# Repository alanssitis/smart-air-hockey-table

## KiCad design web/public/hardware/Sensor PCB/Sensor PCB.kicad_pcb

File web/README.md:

# Better Website

Just a better site in every way.

All settings are set properly for copy-and-paste into the `/web` directory
of the shay drive. All that needs to be done is to build it.

## Installing `npm`

I use `nvm` to manage node versions. My local machine is running `v18.16.0` as
of Sep 5, 2023.

## Building the site

First, install all dependencies with

```
npm install .
```

Than, build the project with

```
npm run build
```

This will create all the requisites in `/dist`. The contents of `/dist` can
be copied to the shay `/web` directory.

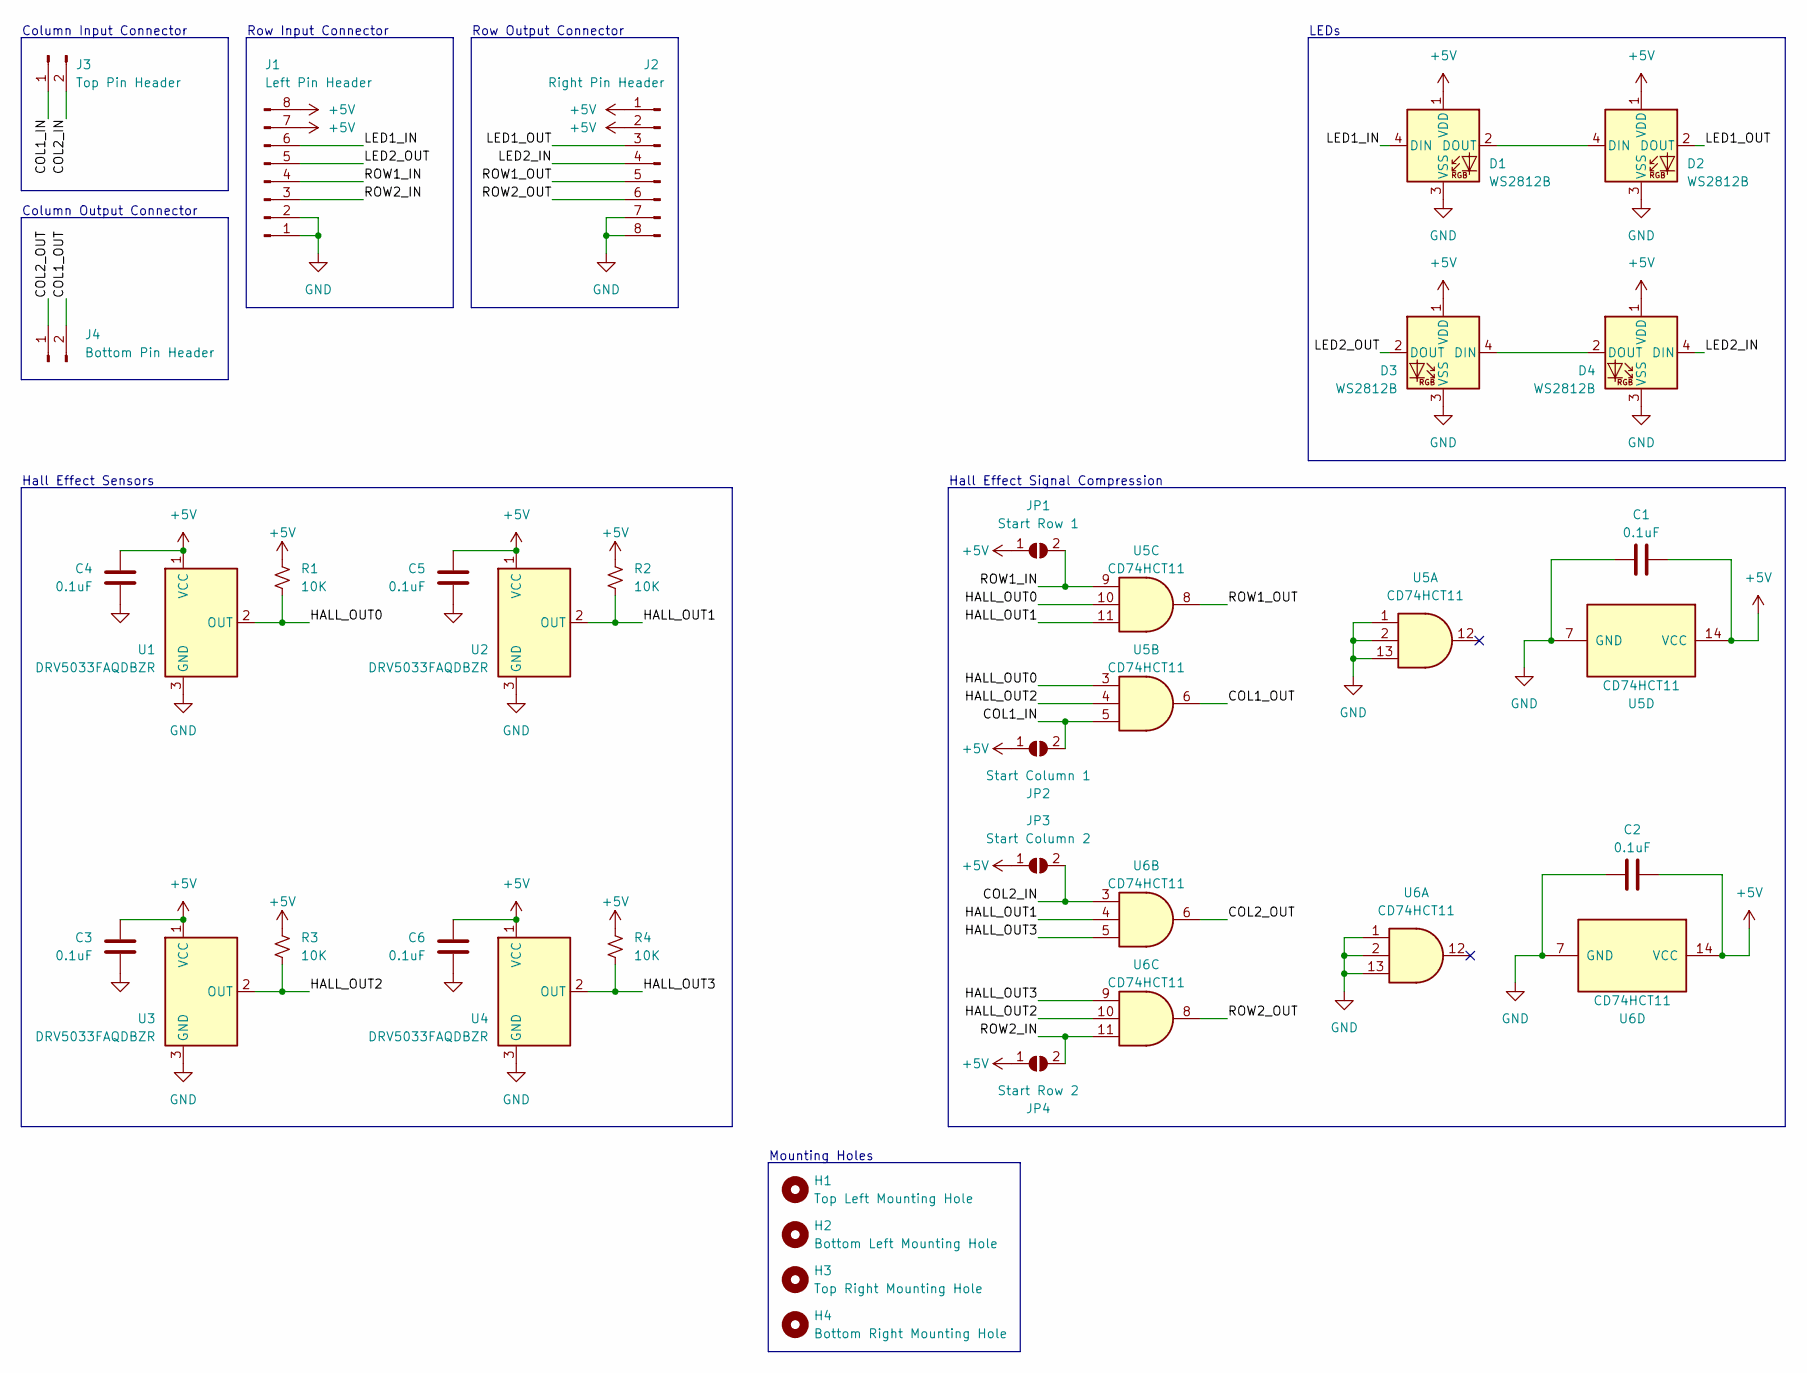
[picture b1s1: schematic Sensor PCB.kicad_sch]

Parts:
C1, C2, C3, C4, C5, C6: 0.1uF; C_0805_2012Metric_Pad1.18x1.45mm_HandSolder; JLCPCB Part # C49678
D1, D2, D3, D4: WS2812B; LED_WS2812B_PLCC4_5.0x5.0mm_P3.2mm; JLCPCB Part # C4154882
H1: Top Left Mounting Hole; MountingHole_2.7mm_M2.5
H2: Bottom Left Mounting Hole; MountingHole_2.7mm_M2.5
H3: Top Right Mounting Hole; MountingHole_2.7mm_M2.5
H4: Bottom Right Mounting Hole; MountingHole_2.7mm_M2.5
J1: Left Pin Header; PinHeader_1x08_P2.54mm_Horizontal; JLCPCB Part # C492416
J2: Right Pin Header; PinHeader_1x08_P2.54mm_Horizontal; JLCPCB Part # C492416
J3: Top Pin Header; PinHeader_1x02_P2.54mm_Horizontal; JLCPCB Part # C492410
J4: Bottom Pin Header; PinHeader_1x02_P2.54mm_Horizontal; JLCPCB Part # C492410
JP1: Start Row 1; SolderJumper-2_P1.3mm_Open_TrianglePad1.0x1.5mm
JP2: Start Column 1; SolderJumper-2_P1.3mm_Open_TrianglePad1.0x1.5mm
JP3: Start Column 2; SolderJumper-2_P1.3mm_Open_TrianglePad1.0x1.5mm
JP4: Start Row 2; SolderJumper-2_P1.3mm_Open_TrianglePad1.0x1.5mm
R1, R2, R3, R4: 10K; R_0805_2012Metric_Pad1.20x1.40mm_HandSolder; JLCPCB Part # C100047
U1, U2, U3, U4: DRV5033FAQDBZR; SOT-23; JLCPCB Part # C2655029
U5, U6: CD74HCT11; SOIC-14_3.9x8.7mm_P1.27mm; JLCPCB Part # C7643

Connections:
+5V: C1.1, C2.1, C3.1, C4.1, C5.1, C6.1, D1.1 (VDD), D2.1 (VDD), D3.1 (VDD), D4.1 (VDD), J1.7, J1.8, J2.1, J2.2, JP1.1 (A), JP2.1 (A), JP3.1 (A), JP4.1 (A), R1.1, R2.1, R3.1, R4.1, U1.1 (VCC), U2.1 (VCC), U3.1 (VCC), U4.1 (VCC), U5.14 (VCC), U6.14 (VCC)
/COL1_IN: J3.1, JP2.2 (B), U5.5
/COL1_OUT: J4.2, U5.6
/COL2_IN: J3.2, JP3.2 (B), U6.3
/COL2_OUT: J4.1, U6.6
/HALL_OUT0: R1.2, U1.2 (OUT), U5.3, U5.10
/HALL_OUT1: R2.2, U2.2 (OUT), U5.11, U6.4
/HALL_OUT2: R3.2, U3.2 (OUT), U5.4, U6.10
/HALL_OUT3: R4.2, U4.2 (OUT), U6.5, U6.9
/LED1_IN: D1.4 (DIN), J1.6
/LED1_OUT: D2.2 (DOUT), J2.3
/LED2_IN: D4.4 (DIN), J2.4
/LED2_OUT: D3.2 (DOUT), J1.5
/ROW1_IN: J1.4, JP1.2 (B), U5.9
/ROW1_OUT: J2.5, U5.8
/ROW2_IN: J1.3, JP4.2 (B), U6.11
/ROW2_OUT: J2.6, U6.8
GND: C1.2, C2.2, C3.2, C4.2, C5.2, C6.2, D1.3 (VSS), D2.3 (VSS), D3.3 (VSS), D4.3 (VSS), J1.1, J1.2, J2.7, J2.8, U1.3 (GND), U2.3 (GND), U3.3 (GND), U4.3 (GND), U5.1, U5.2, U5.7 (GND), U5.13, U6.1, U6.2, U6.7 (GND), U6.13
unnamed: D1.2 (DOUT), D2.4 (DIN)
unnamed: D3.4 (DIN), D4.2 (DOUT)

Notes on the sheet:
Hall Effect Sensors
Column Input Connector
Row Output Connector
Column Output Connector
Hall Effect Signal Compression
Mounting Holes
LEDs
Row Input Connector

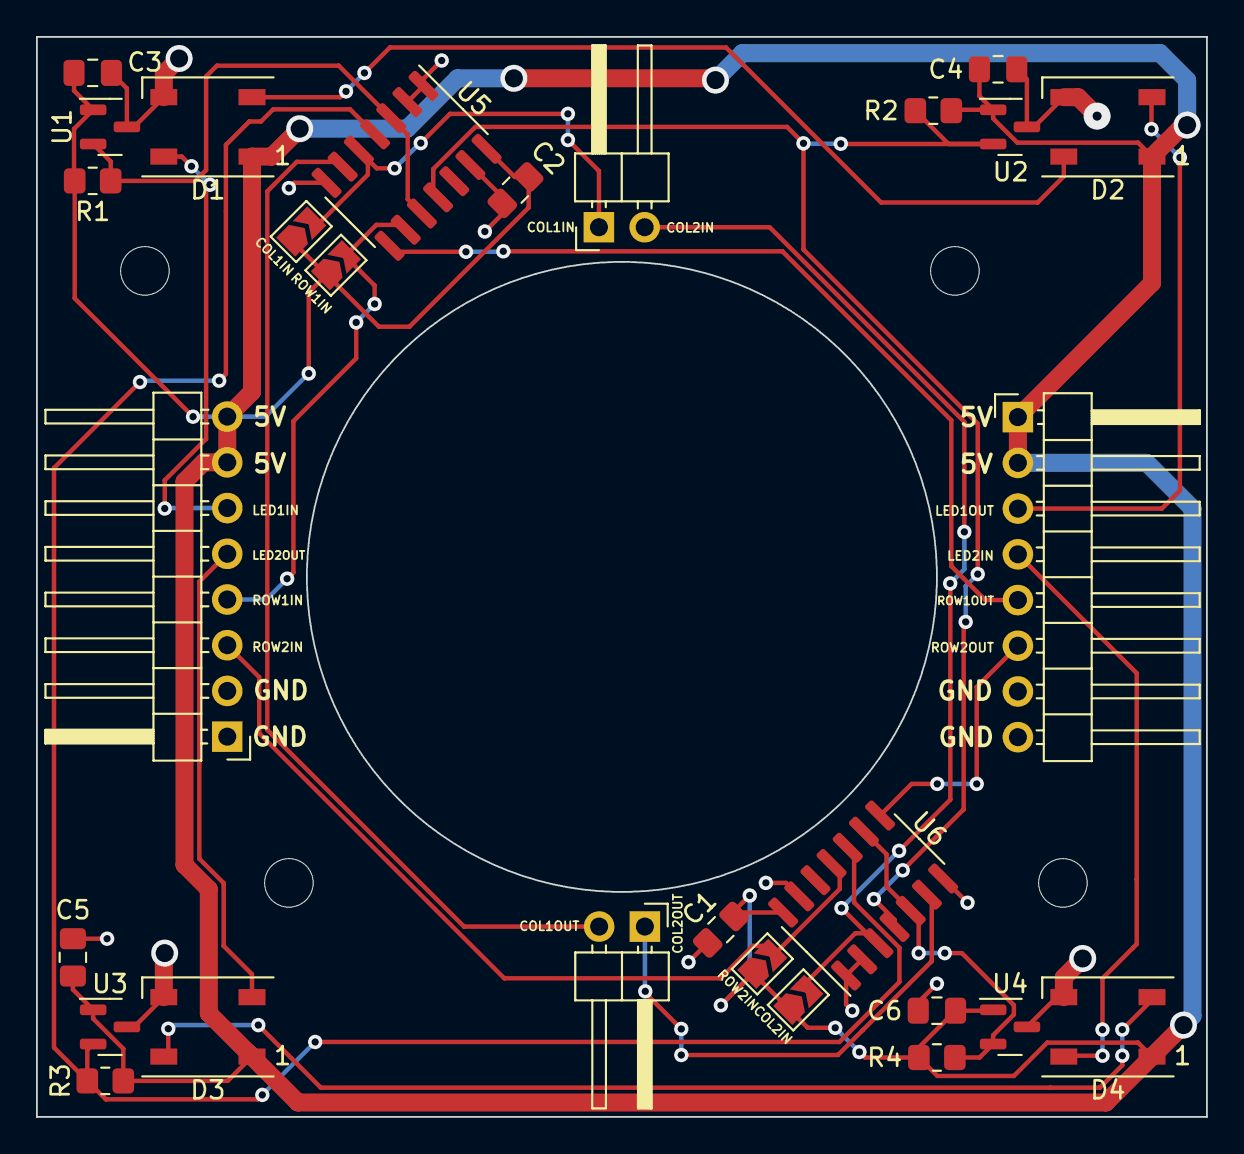
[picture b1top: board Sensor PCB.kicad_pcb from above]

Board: 2 copper layers, 65.0 x 60.0 mm, 32 parts (0 on the bottom side), 20 nets.

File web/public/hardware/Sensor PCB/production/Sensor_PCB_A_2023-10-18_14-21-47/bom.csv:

Designator,Footprint,Quantity,Value,LCSC Part #
"C1, C2, C3, C4, C5, C6",0805,6,0.1uF,C49678
D1,LED_WS2812B_PLCC4_5.0x5.0mm_P3.2mm,1,WS2812B,
"D2, D3, D4",LED_WS2812B_PLCC4_5.0x5.0mm_P3.2mm,3,WS2812B,C4154882
H1,MountingHole_2.7mm_M2.5,1,Top Left Mounting Hole,
H2,MountingHole_2.7mm_M2.5,1,Bottom Left Mounting Hole,
H3,MountingHole_2.7mm_M2.5,1,Top Right Mounting Hole,
H4,MountingHole_2.7mm_M2.5,1,Bottom Right Mounting Hole,
J1,PinHeader_1x08_P2.54mm_Horizontal,1,Left Pin Header,C492416
J2,PinHeader_1x08_P2.54mm_Horizontal,1,Right Pin Header,C492416
J3,PinHeader_1x02_P2.54mm_Horizontal,1,Top Pin Header,C492410
J4,PinHeader_1x02_P2.54mm_Horizontal,1,Bottom Pin Header,C492410
JP1,SolderJumper-2_P1.3mm_Open_TrianglePad1.0x1.5mm,1,Start Row 1,
JP2,SolderJumper-2_P1.3mm_Open_TrianglePad1.0x1.5mm,1,Start Column 1,
JP3,SolderJumper-2_P1.3mm_Open_TrianglePad1.0x1.5mm,1,Start Column 2,
JP4,SolderJumper-2_P1.3mm_Open_TrianglePad1.0x1.5mm,1,Start Row 2,
"R1, R2, R3, R4",0805,4,10K,C100047
"U1, U2, U3, U4",SOT-23,4,DRV5033FAQDBZR,C2655029
"U5, U6",SOIC-14_3.9x8.7mm_P1.27mm,2,CD74HCT11,C7643

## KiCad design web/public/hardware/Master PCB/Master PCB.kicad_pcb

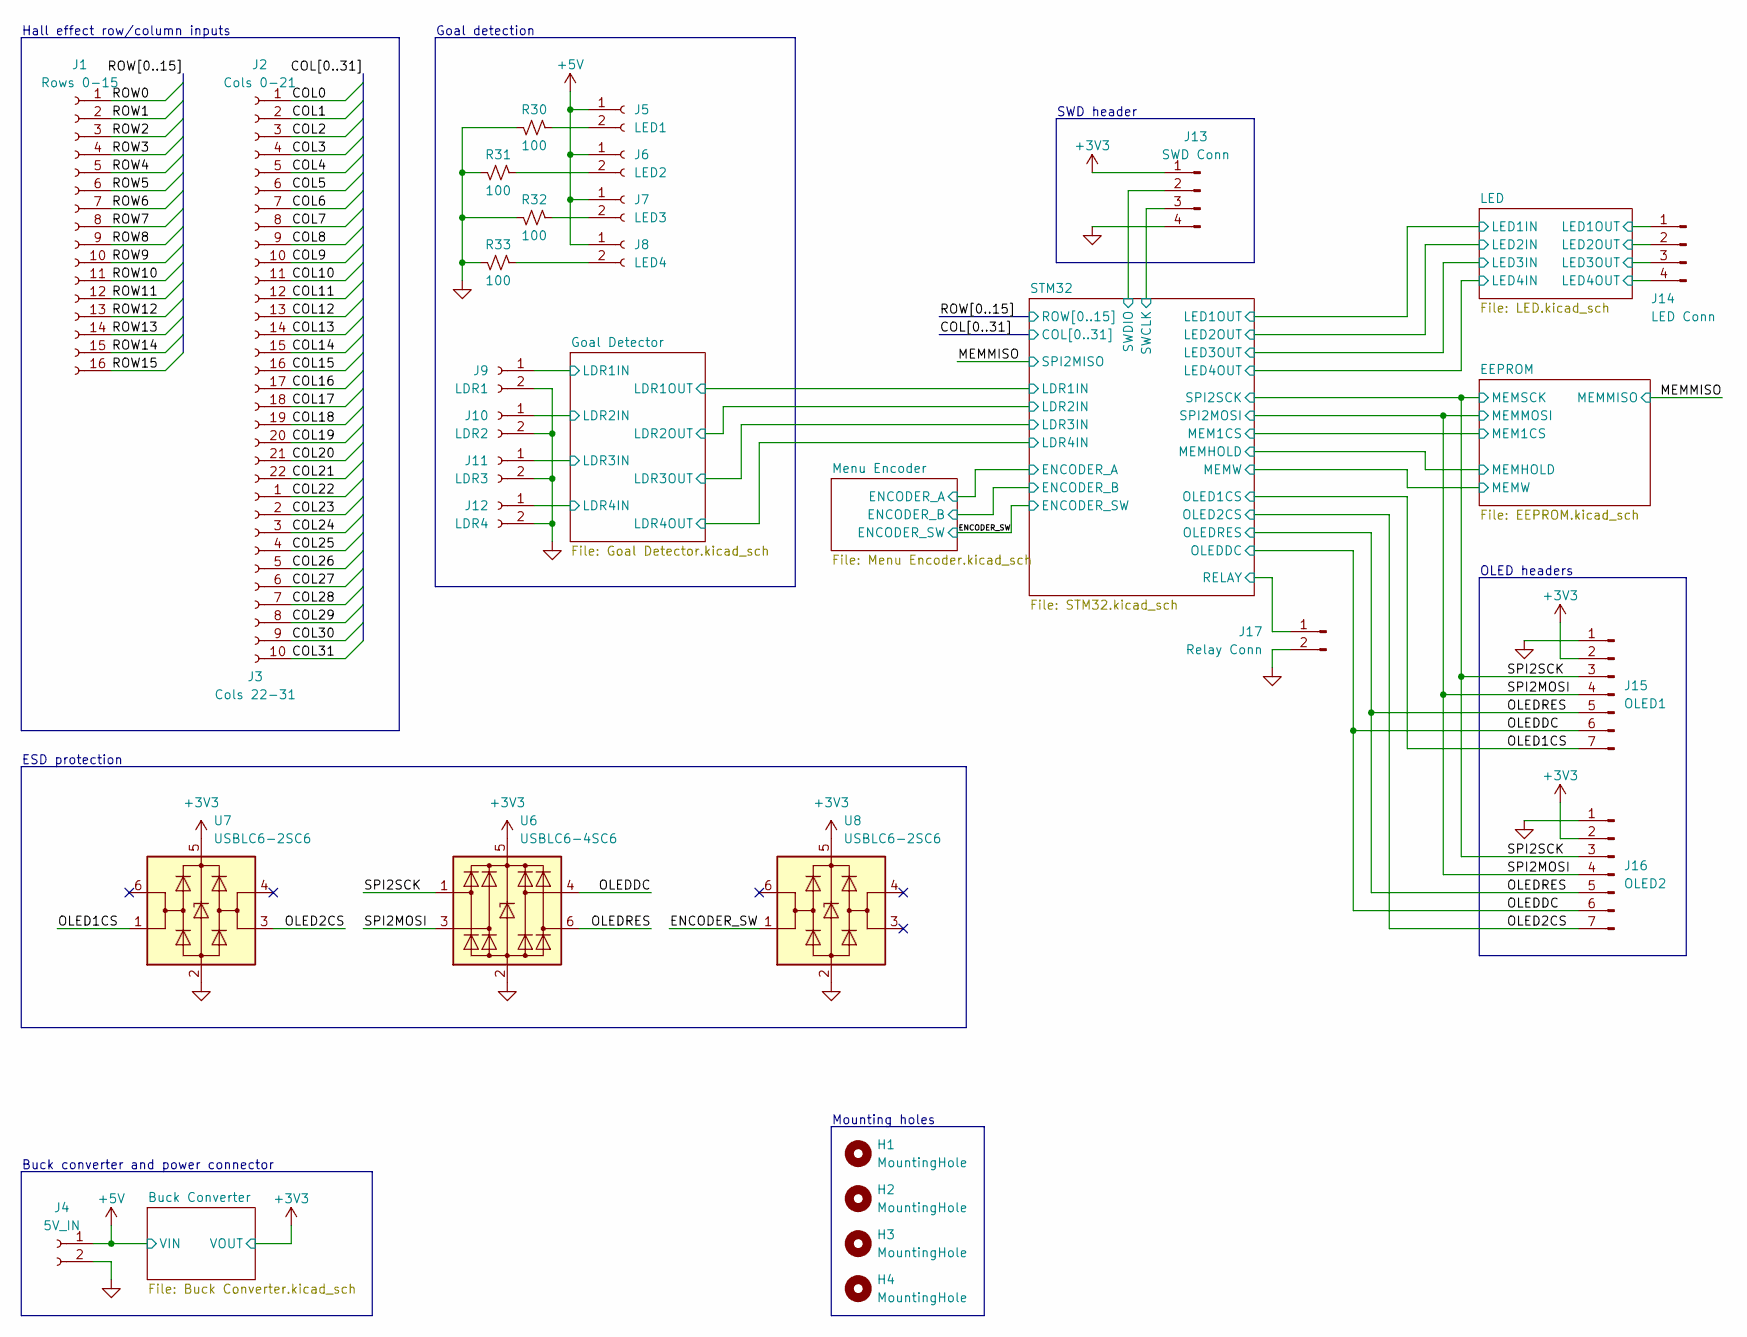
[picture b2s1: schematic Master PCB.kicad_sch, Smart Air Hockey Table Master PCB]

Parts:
H1, H2, H3, H4: MountingHole; MountingHole_3.2mm_M3
J1: Rows 0-15; PinHeader_1x16_P2.54mm_Vertical
J2: Cols 0-21; PinHeader_1x22_P2.54mm_Vertical
J3: Cols 22-31; PinHeader_1x10_P2.54mm_Vertical
J4: 5V_IN; JST_PH_B2B-PH-K_1x02_P2.00mm_Vertical
J5: LED1; JST_PH_B2B-PH-K_1x02_P2.00mm_Vertical
J6: LED2; JST_PH_B2B-PH-K_1x02_P2.00mm_Vertical
J7: LED3; JST_PH_B2B-PH-K_1x02_P2.00mm_Vertical
J8: LED4; JST_PH_B2B-PH-K_1x02_P2.00mm_Vertical
J9: LDR1; JST_PH_B2B-PH-K_1x02_P2.00mm_Vertical
J10: LDR2; JST_PH_B2B-PH-K_1x02_P2.00mm_Vertical
J11: LDR3; JST_PH_B2B-PH-K_1x02_P2.00mm_Vertical
J12: LDR4; JST_PH_B2B-PH-K_1x02_P2.00mm_Vertical
J13: SWD Conn; PinHeader_1x04_P2.54mm_Vertical
J14: LED Conn; PinHeader_1x04_P2.54mm_Vertical
J15: OLED1; JST_PH_B7B-PH-K_1x07_P2.00mm_Vertical
J16: OLED2; JST_PH_B7B-PH-K_1x07_P2.00mm_Vertical
J17: Relay Conn; JST_PH_B2B-PH-K_1x02_P2.00mm_Vertical
R30, R31, R32, R33: 100; R_0805_2012Metric_Pad1.20x1.40mm_HandSolder
U6: USBLC6-4SC6; SOT-23-6
U7, U8: USBLC6-2SC6; SOT-23-6

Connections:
/COL0: J2.1; also elsewhere on the board
/COL1: J2.2; also elsewhere on the board
/COL2: J2.3; also elsewhere on the board
/COL3: J2.4; also elsewhere on the board
/COL4: J2.5; also elsewhere on the board
/COL5: J2.6; also elsewhere on the board
/COL6: J2.7; also elsewhere on the board
/COL7: J2.8; also elsewhere on the board
/COL8: J2.9; also elsewhere on the board
/COL9: J2.10; also elsewhere on the board
/COL10: J2.11; also elsewhere on the board
/COL11: J2.12; also elsewhere on the board
/COL12: J2.13; also elsewhere on the board
/COL13: J2.14; also elsewhere on the board
/COL14: J2.15; also elsewhere on the board
/COL15: J2.16; also elsewhere on the board
/COL16: J2.17; also elsewhere on the board
/COL17: J2.18; also elsewhere on the board
/COL18: J2.19; also elsewhere on the board
/COL19: J2.20; also elsewhere on the board
/COL20: J2.21; also elsewhere on the board
/COL21: J2.22; also elsewhere on the board
/COL22: J3.1; also elsewhere on the board
/COL23: J3.2; also elsewhere on the board
/COL24: J3.3; also elsewhere on the board
/COL25: J3.4; also elsewhere on the board
/COL26: J3.5; also elsewhere on the board
/COL27: J3.6; also elsewhere on the board
/COL28: J3.7; also elsewhere on the board
/COL29: J3.8; also elsewhere on the board
/COL30: J3.9; also elsewhere on the board
/COL31: J3.10; also elsewhere on the board
/ENCODER_SW: U8.1 (I/O1); also elsewhere on the board
/Goal Detector/LDR1IN: J9.1; also elsewhere on the board
/Goal Detector/LDR2IN: J10.1; also elsewhere on the board
/Goal Detector/LDR3IN: J11.1; also elsewhere on the board
/Goal Detector/LDR4IN: J12.1; also elsewhere on the board
/LED/LED1OUT: J14.1; also elsewhere on the board
/LED/LED2OUT: J14.2; also elsewhere on the board
/LED/LED3OUT: J14.3; also elsewhere on the board
/LED/LED4OUT: J14.4; also elsewhere on the board
/OLED1CS: J15.7, U7.1 (I/O1); also elsewhere on the board
/OLED2CS: J16.7, U7.3 (I/O2); also elsewhere on the board
/OLEDDC: J15.6, J16.6, U6.4 (I/O3); also elsewhere on the board
/OLEDRES: J15.5, J16.5, U6.6 (I/O4); also elsewhere on the board
/ROW0: J1.1; also elsewhere on the board
/ROW1: J1.2; also elsewhere on the board
/ROW2: J1.3; also elsewhere on the board
/ROW3: J1.4; also elsewhere on the board
/ROW4: J1.5; also elsewhere on the board
/ROW5: J1.6; also elsewhere on the board
/ROW6: J1.7; also elsewhere on the board
/ROW7: J1.8; also elsewhere on the board
/ROW8: J1.9; also elsewhere on the board
/ROW9: J1.10; also elsewhere on the board
/ROW10: J1.11; also elsewhere on the board
/ROW11: J1.12; also elsewhere on the board
/ROW12: J1.13; also elsewhere on the board
/ROW13: J1.14; also elsewhere on the board
/ROW14: J1.15; also elsewhere on the board
/ROW15: J1.16; also elsewhere on the board
/SPI2SCK: J15.3, J16.3, U6.1 (I/O1); also elsewhere on the board
/STM32/RELAY: J17.1; also elsewhere on the board
/STM32/SWCLK: J13.3; also elsewhere on the board
/STM32/SWDIO: J13.2; also elsewhere on the board
unnamed: J5.2, R30.1
unnamed: J6.2, R31.1
unnamed: J7.2, R32.1
unnamed: J8.2, R33.1

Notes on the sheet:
Mounting holes
Hall effect row/column inputs
SWD header
ESD protection
OLED headers
Buck converter and power connector
Goal detection

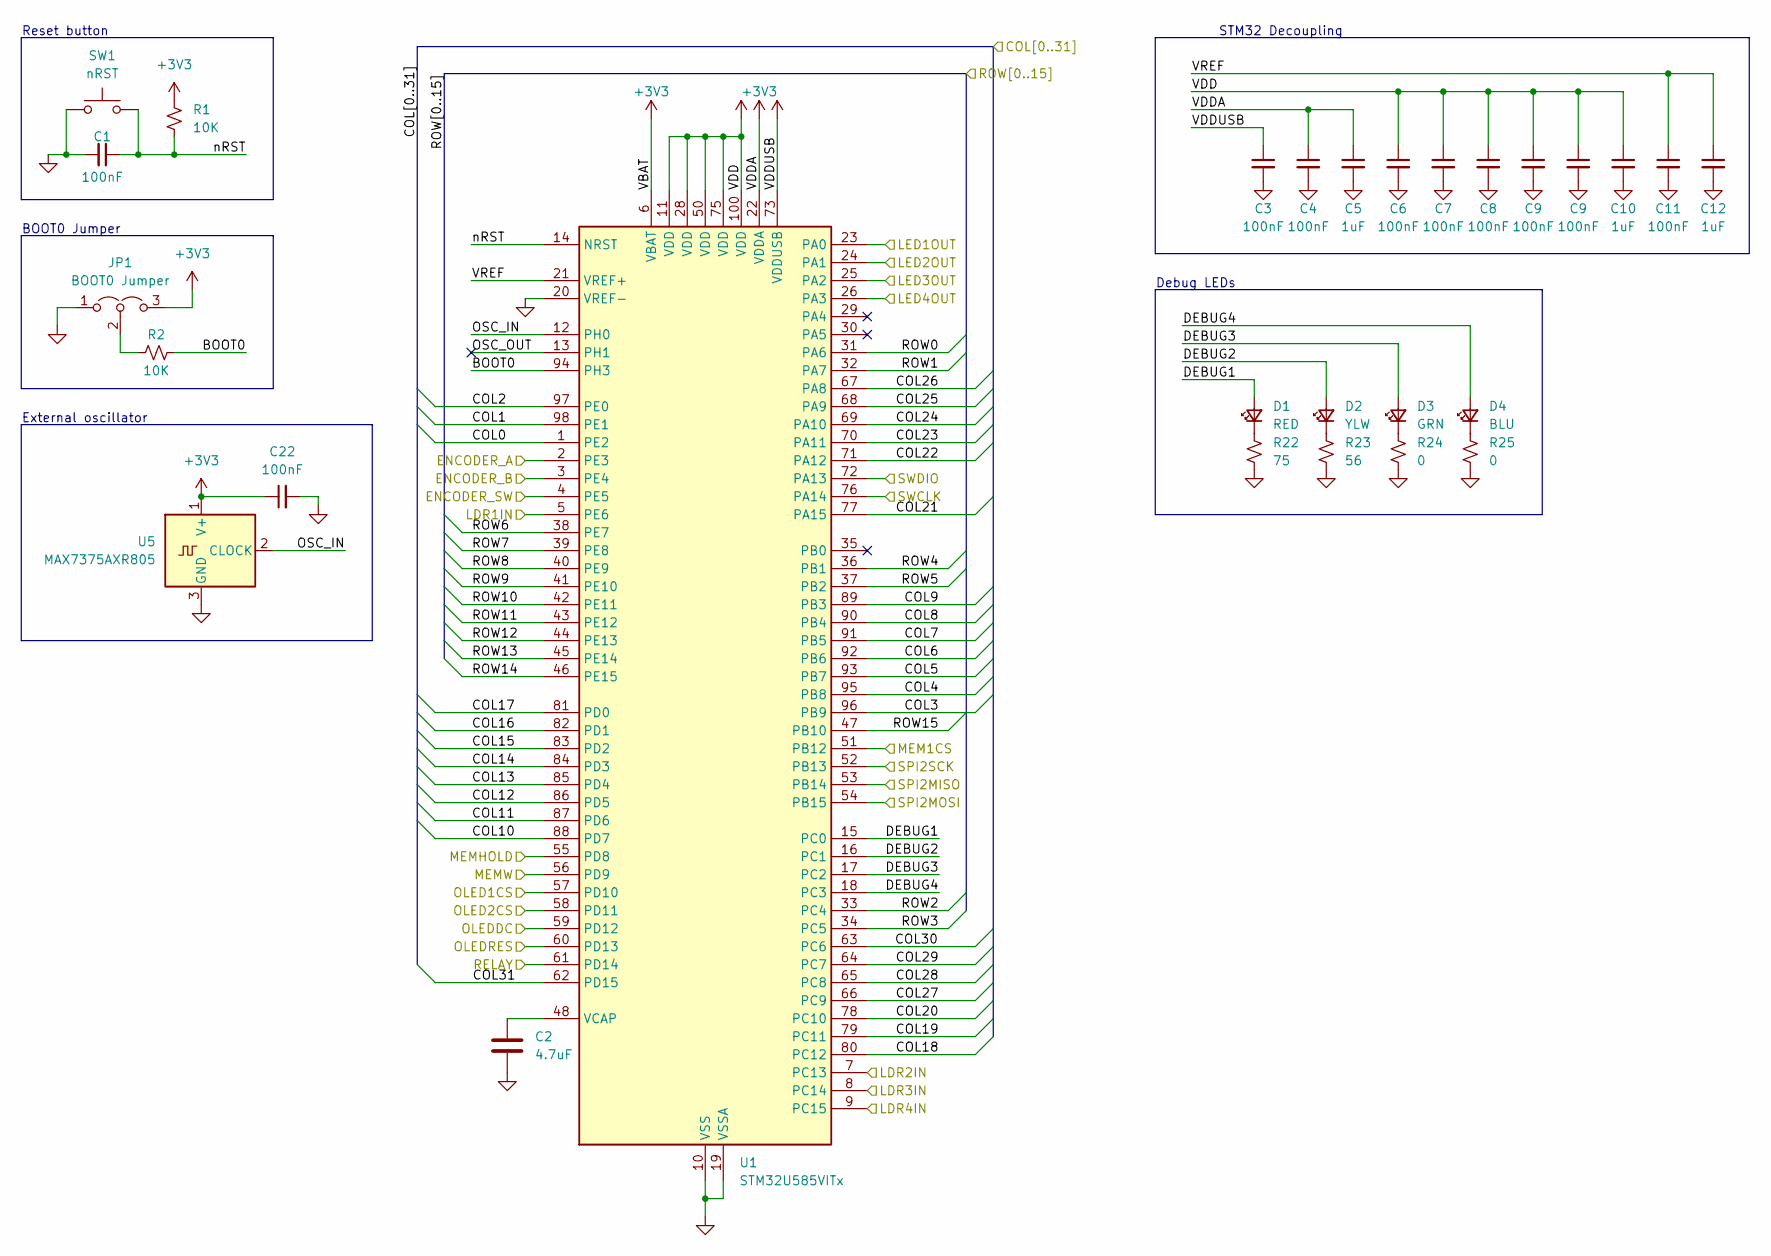
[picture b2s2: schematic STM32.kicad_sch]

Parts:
C1, C3, C4, C6, C7, C8, C9, C11, C22: 100nF; C_0805_2012Metric_Pad1.18x1.45mm_HandSolder
C2: 4.7uF; C_0805_2012Metric_Pad1.18x1.45mm_HandSolder
C5, C10, C12: 1uF; C_0805_2012Metric_Pad1.18x1.45mm_HandSolder
D1: RED; LED_0805_2012Metric_Pad1.15x1.40mm_HandSolder
D2: YLW; LED_0805_2012Metric_Pad1.15x1.40mm_HandSolder
D3: GRN; LED_0805_2012Metric_Pad1.15x1.40mm_HandSolder
D4: BLU; LED_0805_2012Metric_Pad1.15x1.40mm_HandSolder
JP1: BOOT0 Jumper; PinHeader_1x03_P2.54mm_Vertical
R1, R2: 10K; R_0805_2012Metric_Pad1.20x1.40mm_HandSolder
R22: 75; R_0805_2012Metric_Pad1.20x1.40mm_HandSolder
R23: 56; R_0805_2012Metric_Pad1.20x1.40mm_HandSolder
R24, R25: 0; R_0805_2012Metric_Pad1.20x1.40mm_HandSolder
SW1: nRST; SW_PUSH_6mm
U1: STM32U585VITx; LQFP-100_14x14mm_P0.5mm
U5: MAX7375AXR805; SOT-323_SC-70

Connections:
/COL0: U1.1 (PE2); also elsewhere on the board
/COL1: U1.98 (PE1); also elsewhere on the board
/COL2: U1.97 (PE0); also elsewhere on the board
/COL3: U1.96 (PB9); also elsewhere on the board
/COL4: U1.95 (PB8); also elsewhere on the board
/COL5: U1.93 (PB7); also elsewhere on the board
/COL6: U1.92 (PB6); also elsewhere on the board
/COL7: U1.91 (PB5); also elsewhere on the board
/COL8: U1.90 (PB4); also elsewhere on the board
/COL9: U1.89 (PB3); also elsewhere on the board
/COL10: U1.88 (PD7); also elsewhere on the board
/COL11: U1.87 (PD6); also elsewhere on the board
/COL12: U1.86 (PD5); also elsewhere on the board
/COL13: U1.85 (PD4); also elsewhere on the board
/COL14: U1.84 (PD3); also elsewhere on the board
/COL15: U1.83 (PD2); also elsewhere on the board
/COL16: U1.82 (PD1); also elsewhere on the board
/COL17: U1.81 (PD0); also elsewhere on the board
/COL18: U1.80 (PC12); also elsewhere on the board
/COL19: U1.79 (PC11); also elsewhere on the board
/COL20: U1.78 (PC10); also elsewhere on the board
/COL21: U1.77 (PA15); also elsewhere on the board
/COL22: U1.71 (PA12); also elsewhere on the board
/COL23: U1.70 (PA11); also elsewhere on the board
/COL24: U1.69 (PA10); also elsewhere on the board
/COL25: U1.68 (PA9); also elsewhere on the board
/COL26: U1.67 (PA8); also elsewhere on the board
/COL27: U1.66 (PC9); also elsewhere on the board
/COL28: U1.65 (PC8); also elsewhere on the board
/COL29: U1.64 (PC7); also elsewhere on the board
/COL30: U1.63 (PC6); also elsewhere on the board
/COL31: U1.62 (PD15); also elsewhere on the board
/EEPROM/MEMHOLD: U1.55 (PD8); also elsewhere on the board
/ENCODER_SW: U1.4 (PE5); also elsewhere on the board
/Goal Detector/LDR1OUT: U1.5 (PE6); also elsewhere on the board
/Goal Detector/LDR2OUT: U1.7 (PC13); also elsewhere on the board
/Goal Detector/LDR3OUT: U1.8 (PC14); also elsewhere on the board
/Goal Detector/LDR4OUT: U1.9 (PC15); also elsewhere on the board
/LED/LED1IN: U1.23 (PA0); also elsewhere on the board
/LED/LED2IN: U1.24 (PA1); also elsewhere on the board
/LED/LED3IN: U1.25 (PA2); also elsewhere on the board
/LED/LED4IN: U1.26 (PA3); also elsewhere on the board
/Menu Encoder/ENCODER_A: U1.2 (PE3); also elsewhere on the board
/Menu Encoder/ENCODER_B: U1.3 (PE4); also elsewhere on the board
/OLED1CS: U1.57 (PD10); also elsewhere on the board
/OLED2CS: U1.58 (PD11); also elsewhere on the board
/OLEDDC: U1.59 (PD12); also elsewhere on the board
/OLEDRES: U1.60 (PD13); also elsewhere on the board
/ROW0: U1.31 (PA6); also elsewhere on the board
/ROW1: U1.32 (PA7); also elsewhere on the board
/ROW2: U1.33 (PC4); also elsewhere on the board
/ROW3: U1.34 (PC5); also elsewhere on the board
/ROW4: U1.36 (PB1); also elsewhere on the board
/ROW5: U1.37 (PB2); also elsewhere on the board
/ROW6: U1.38 (PE7); also elsewhere on the board
/ROW7: U1.39 (PE8); also elsewhere on the board
/ROW8: U1.40 (PE9); also elsewhere on the board
/ROW9: U1.41 (PE10); also elsewhere on the board
/ROW10: U1.42 (PE11); also elsewhere on the board
/ROW11: U1.43 (PE12); also elsewhere on the board
/ROW12: U1.44 (PE13); also elsewhere on the board
/ROW13: U1.45 (PE14); also elsewhere on the board
/ROW14: U1.46 (PE15); also elsewhere on the board
/ROW15: U1.47 (PB10); also elsewhere on the board
/SPI2SCK: U1.52 (PB13); also elsewhere on the board
/STM32/DEBUG1: D1.2 (A), U1.15 (PC0)
/STM32/DEBUG2: D2.2 (A), U1.16 (PC1)
/STM32/DEBUG3: D3.2 (A), U1.17 (PC2)
/STM32/DEBUG4: D4.2 (A), U1.18 (PC3)
/STM32/OSC_IN: U1.12 (PH0), U5.2 (CLOCK)
/STM32/OSC_OUT: U1.13 (PH1)
/STM32/RELAY: U1.61 (PD14); also elsewhere on the board
/STM32/SWCLK: U1.76 (PA14); also elsewhere on the board
/STM32/SWDIO: U1.72 (PA13); also elsewhere on the board
/STM32/VREF: C11.1, C12.1, U1.21 (VREF+)
unnamed: D1.1 (K), R22.1
unnamed: D2.1 (K), R23.1
unnamed: D3.1 (K), R24.1
unnamed: D4.1 (K), R25.1
unnamed: C2.1, U1.48 (VCAP)

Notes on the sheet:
Reset button
External oscillator
BOOT0 Jumper
STM32 Decoupling
Debug LEDs

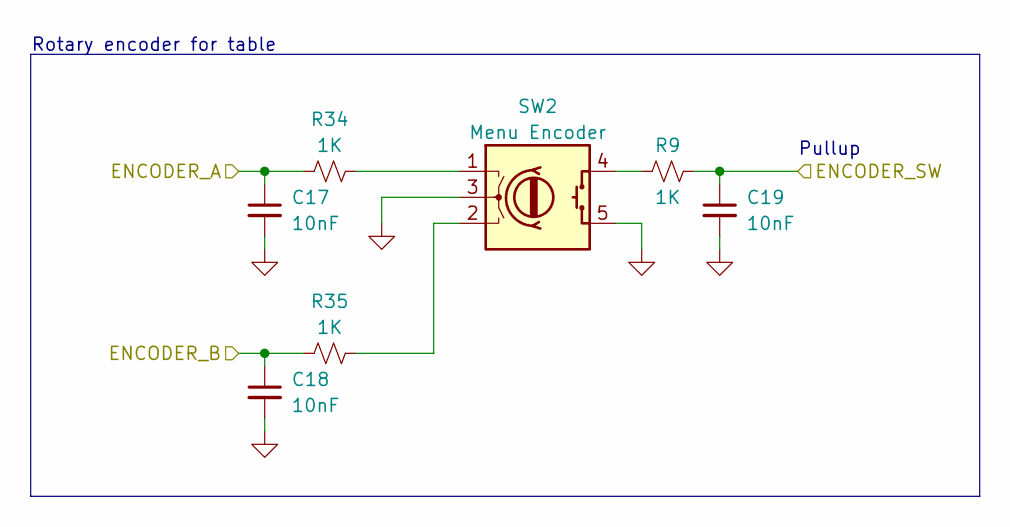
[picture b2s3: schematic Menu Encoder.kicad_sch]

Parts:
C17, C18, C19: 10nF; C_0805_2012Metric_Pad1.18x1.45mm_HandSolder
R9, R34, R35: 1K; R_0805_2012Metric_Pad1.20x1.40mm_HandSolder
SW2: Menu Encoder; JST_PH_B5B-PH-K_1x05_P2.00mm_Vertical

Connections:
/ENCODER_SW: C19.1, R9.2; also elsewhere on the board
/Menu Encoder/ENCODER_A: C17.1, R34.1; also elsewhere on the board
/Menu Encoder/ENCODER_B: C18.1, R35.1; also elsewhere on the board
unnamed: R34.2, SW2.1 (A)
unnamed: R35.2, SW2.2 (B)
unnamed: R9.1, SW2.4 (S1)

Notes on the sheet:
Rotary encoder for table
Pullup

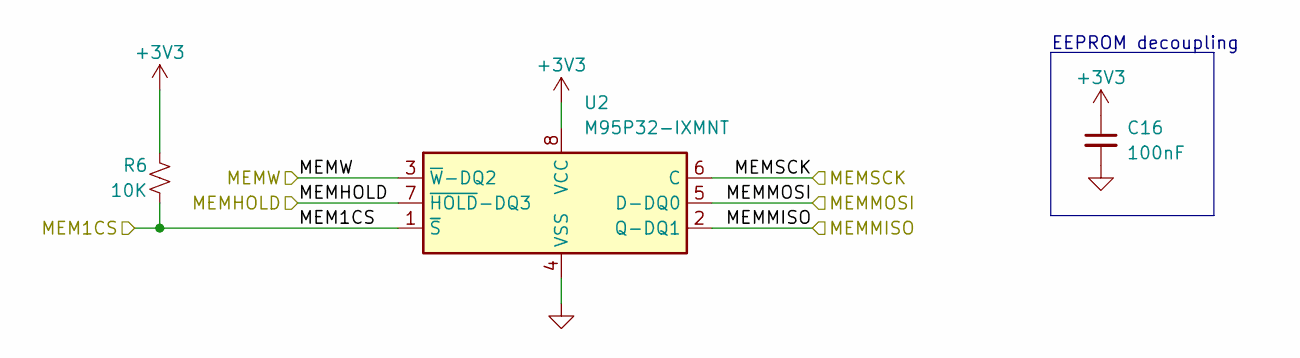
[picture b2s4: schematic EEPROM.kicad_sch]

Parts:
C16: 100nF; C_0805_2012Metric_Pad1.18x1.45mm_HandSolder
R6: 10K; R_0805_2012Metric_Pad1.20x1.40mm_HandSolder
U2: M95P32-IXMNT; SO-8_3.9x4.9mm_P1.27mm

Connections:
/EEPROM/MEMHOLD: U2.7 (~HOLD-DQ3); also elsewhere on the board
/SPI2SCK: U2.6 (C); also elsewhere on the board

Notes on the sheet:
EEPROM decoupling

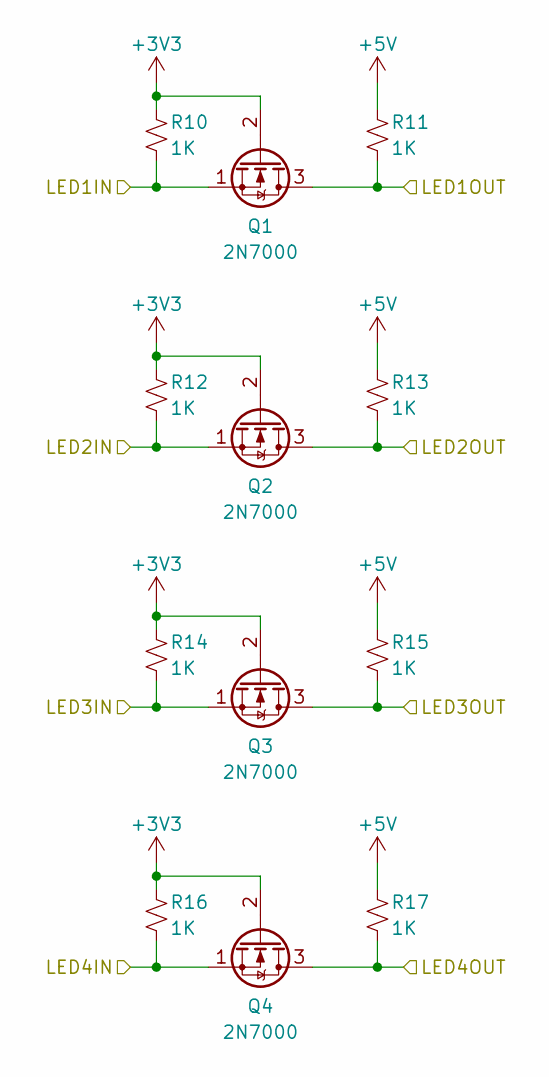
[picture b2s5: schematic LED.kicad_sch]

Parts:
Q1, Q2, Q3, Q4: 2N7000; TO-92_Inline
R10, R11, R12, R13, R14, R15, R16, R17: 1K; R_0805_2012Metric_Pad1.20x1.40mm_HandSolder

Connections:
/LED/LED1IN: Q1.1 (S), R10.2; also elsewhere on the board
/LED/LED1OUT: Q1.3 (D), R11.2; also elsewhere on the board
/LED/LED2IN: Q2.1 (S), R12.2; also elsewhere on the board
/LED/LED2OUT: Q2.3 (D), R13.2; also elsewhere on the board
/LED/LED3IN: Q3.1 (S), R14.2; also elsewhere on the board
/LED/LED3OUT: Q3.3 (D), R15.2; also elsewhere on the board
/LED/LED4IN: Q4.1 (S), R16.2; also elsewhere on the board
/LED/LED4OUT: Q4.3 (D), R17.2; also elsewhere on the board

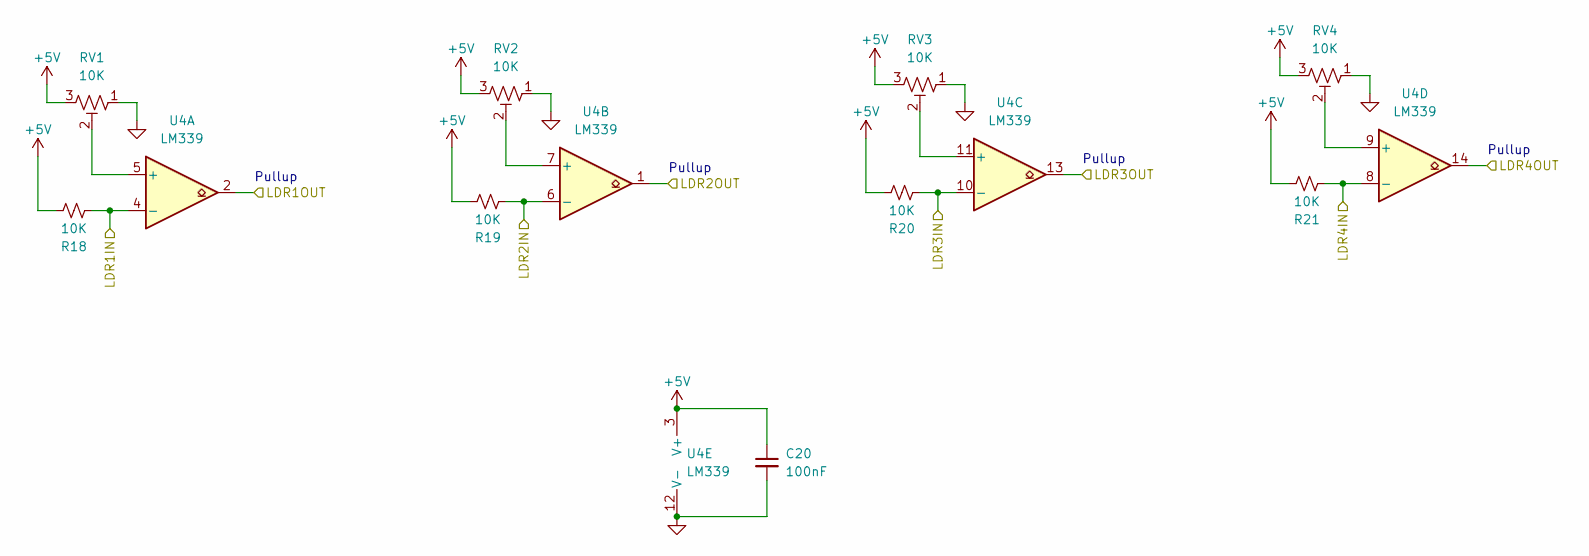
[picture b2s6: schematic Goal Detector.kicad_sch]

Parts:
C20: 100nF; C_0805_2012Metric_Pad1.18x1.45mm_HandSolder
R18, R19, R20, R21: 10K; R_0805_2012Metric_Pad1.20x1.40mm_HandSolder
RV1, RV2, RV3, RV4: 10K; Potentiometer_Bourns_3296W_Vertical
U4: LM339; TSSOP-14_4.4x5mm_P0.65mm

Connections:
/Goal Detector/LDR1IN: R18.1, U4.4 (-); also elsewhere on the board
/Goal Detector/LDR1OUT: U4.2; also elsewhere on the board
/Goal Detector/LDR2IN: R19.1, U4.6 (-); also elsewhere on the board
/Goal Detector/LDR2OUT: U4.1; also elsewhere on the board
/Goal Detector/LDR3IN: R20.1, U4.10 (-); also elsewhere on the board
/Goal Detector/LDR3OUT: U4.13; also elsewhere on the board
/Goal Detector/LDR4IN: R21.1, U4.8 (-); also elsewhere on the board
/Goal Detector/LDR4OUT: U4.14; also elsewhere on the board
unnamed: RV1.2, U4.5 (+)
unnamed: RV2.2, U4.7 (+)
unnamed: RV3.2, U4.11 (+)
unnamed: RV4.2, U4.9 (+)

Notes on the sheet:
Pullup

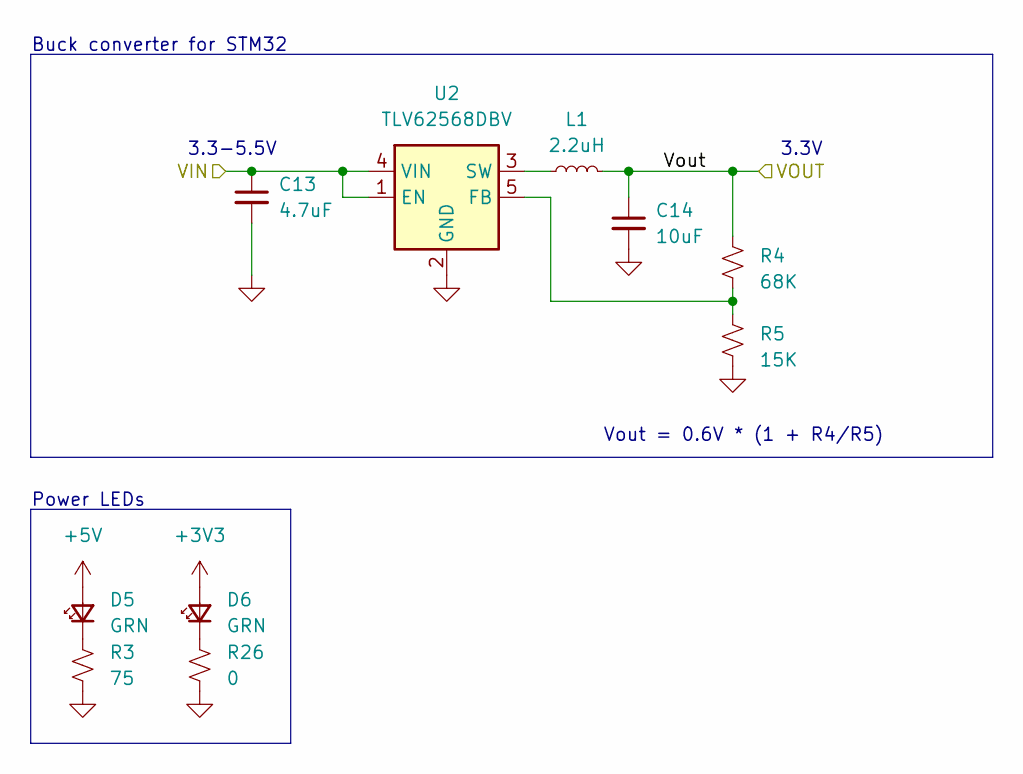
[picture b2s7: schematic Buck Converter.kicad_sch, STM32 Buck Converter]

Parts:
C13: 4.7uF; C_0805_2012Metric_Pad1.18x1.45mm_HandSolder
C14: 10uF; C_0805_2012Metric_Pad1.18x1.45mm_HandSolder
D5, D6: GRN; LED_0805_2012Metric_Pad1.15x1.40mm_HandSolder
L1: 2.2uH; L_4.0x4.0_H1.8
R3: 75; R_0805_2012Metric_Pad1.20x1.40mm_HandSolder
R4: 68K; R_0805_2012Metric_Pad1.20x1.40mm_HandSolder
R5: 15K; R_0805_2012Metric_Pad1.20x1.40mm_HandSolder
R26: 0; R_0805_2012Metric_Pad1.20x1.40mm_HandSolder
U2: TLV62568DBV; SOT-23-5

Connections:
unnamed: D5.1 (K), R3.1
unnamed: D6.1 (K), R26.1

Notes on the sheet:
Vout = 0.6V * (1 + R4/R5)
3.3V
Power LEDs
Buck converter for STM32
3.3-5.5V

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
